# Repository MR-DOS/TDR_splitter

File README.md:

# TDR-splitter
----
## Description
Addon to te TDR_avalanche to allow simple measurement of cable reflections.

----
## Overview
This board should be used with the TDR-avalanche to measure cable reflections. The PCB includes trigger generator for the TDR_avalanche, passthrough USB for power supply and resistive splitter to allow connecting a cable and 50 Ohm terminated oscilloscope. The splitter offers 3 ports, 50 Ohm terminated. The signal passes directly over the CABLE port. Insertion loss of the splitter from IN to OUT port is about 20 dB.

----
## Features
### Resistive splitter
Already explained in overview.

### Trigger generator
The trigger generator can output 2, 4 or 8 kHz square wave. 8 kHz is recommended for the TDR_avalanche.

----
## How to use it with TDR_avalanche
Connect TDR_avalanche to the IN port and TRIG\_OUT port. Connect Mini USB B cable as power supply. Connect USB cable to the USB A port and connect the cable to TDR\_avalanche. Connect cable under test to CABLE port. Connect 50 Ohm terminated oscilloscope to the OUT port. Connect second oscilloscope input or trigger to SYNC\_OUT port of TDR\_avalanche. The TDR\_avalanche has to be modified to be usable with this board due to the high insertion loss - you have to remove both the attenuators so that in the emitter there are only the 2x 47R resistors and compensation network and there should be 27 Ohm resistor between output and the emitter network so that it is roughly 50 Ohm terminated (in fact, the termination heavily changes during the avalanche pulse, but this does not matter as long as reflections return after the pulse ends).

----
## How to use it with some other pulse generator
Connect pulser output to IN port, connect cable under test to the CABLE port. Connect oscilloscope to the OUT port. Separate trigger has to be provided by your pulser board.

----
## Images
Oscillogram of an unterminated (open) 50 Ohm cable:

Oscillogram of an unterminated (open) 50 Ohm cable with defect some 35 cm form the end caused by being heavily pressed using pliers:

Closeup of the assembled board with all cables connected (please note that the bad IC footprint is already corrected):

Both the TDR\_avalanche and TDR\_splitter connected:

----
## References
Sadly, nothing interesting here. I came up with the splitter in my head at 4AM in bed.

[Tweet with photos of the device in use](https://twitter.com/polasek_petr/status/1066757945915072512)

----
## Sidenotes
The PCB uses coplanar waveguide designed for use on standard 1.5 mm FR-4 substrate with 35 um copper (double-sided). It is not very carefully designed and does not give perfect match, but as a prototype, its performance was sufficient. You can modify it for whatever impedance you want, just follow this rule: connect parallel to each of the terminal ports resistor equal to 2x the load impedance, the series resistors should be 4/3x the load impedance and don't forget to update the coplanar waveguide according to the desired impedance.

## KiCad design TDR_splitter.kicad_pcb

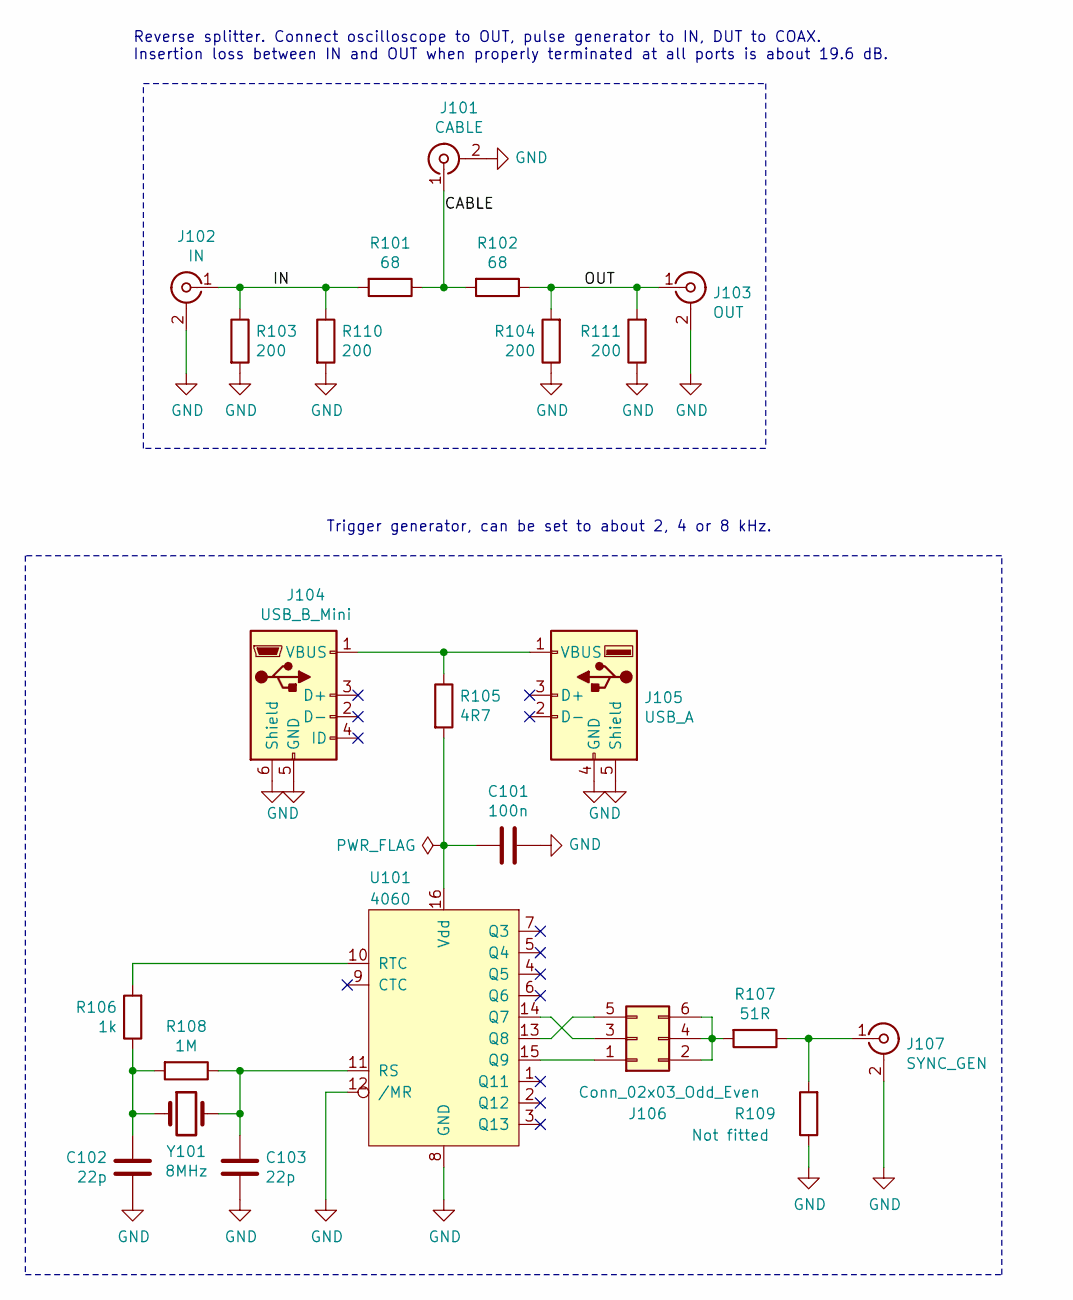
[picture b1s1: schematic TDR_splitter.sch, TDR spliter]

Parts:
C101: 100n; C_0805_2012Metric_Pad1.15x1.40mm_HandSolder
C102, C103: 22p; C_0805_2012Metric_Pad1.15x1.40mm_HandSolder
J101: CABLE; Molex_SMA_Jack_Edge_Mount_Chinese
J102: IN; Molex_SMA_Jack_Edge_Mount_Chinese
J103: OUT; Molex_SMA_Jack_Edge_Mount_Chinese
J104: USB_B_Mini; USB_Mini-B_Lumberg_2486_01_Horizontal
J105: USB_A; USB_A_CNCTech_1001-011-01101_Horizontal
J106: Conn_02x03_Odd_Even; PinHeader_2x03_P2.54mm_Vertical_SMD
J107: SYNC_GEN; Molex_SMA_Jack_Edge_Mount_Chinese
R101, R102: 68; R_0805_2012Metric_Pad1.15x1.40mm_HandSolder
R103, R104, R110, R111: 200; R_0805_2012Metric_Pad1.15x1.40mm_HandSolder
R105: 4R7; R_0805_2012Metric_Pad1.15x1.40mm_HandSolder
R106: 1k; R_0805_2012Metric_Pad1.15x1.40mm_HandSolder
R107: 51R; R_0805_2012Metric_Pad1.15x1.40mm_HandSolder
R108: 1M; R_0805_2012Metric_Pad1.15x1.40mm_HandSolder
R109: Not fitted; R_0805_2012Metric_Pad1.15x1.40mm_HandSolder
U101: 4060; SOIC-16_3.9x9.9mm_P1.27mm
Y101: 8MHz; Crystal_SMD_HC49-SD_HandSoldering

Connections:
/CABLE: J101.1 (In), R101.1, R102.2
/IN: J102.1 (In), R101.2, R103.1, R110.1
/OUT: J103.1 (In), R102.1, R104.2, R111.2
GND: C101.1, C102.2, C103.2, J101.2 (Ext), J102.2 (Ext), J103.2 (Ext), J104.5 (GND), J104.6 (Shield), J105.4 (GND), J105.5 (Shield), J107.2 (Ext), R103.2, R104.1, R109.1, R110.2, R111.1, U101.8 (GND), U101.12 (/MR)
unnamed: C101.2, R105.2, U101.16 (Vdd)
unnamed: C102.1, R106.1, R108.2, Y101.1
unnamed: C103.1, R108.1, U101.11 (RS), Y101.2
unnamed: J104.1 (VBUS), J105.1 (VBUS), R105.1
unnamed: J106.1, U101.15 (Q9)
unnamed: J106.2, J106.4, J106.6, R107.2
unnamed: J106.3, U101.14 (Q7)
unnamed: J106.5, U101.13 (Q8)
unnamed: J107.1 (In), R107.1, R109.2
unnamed: R106.2, U101.10 (RTC)

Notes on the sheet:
Trigger generator, can be set to about 2, 4 or 8 kHz.
Reverse splitter. Connect oscilloscope to OUT, pulse generator to IN, DUT to COAX. Insertion loss between IN and OUT when properly terminated at all ports is about 19.6 dB.

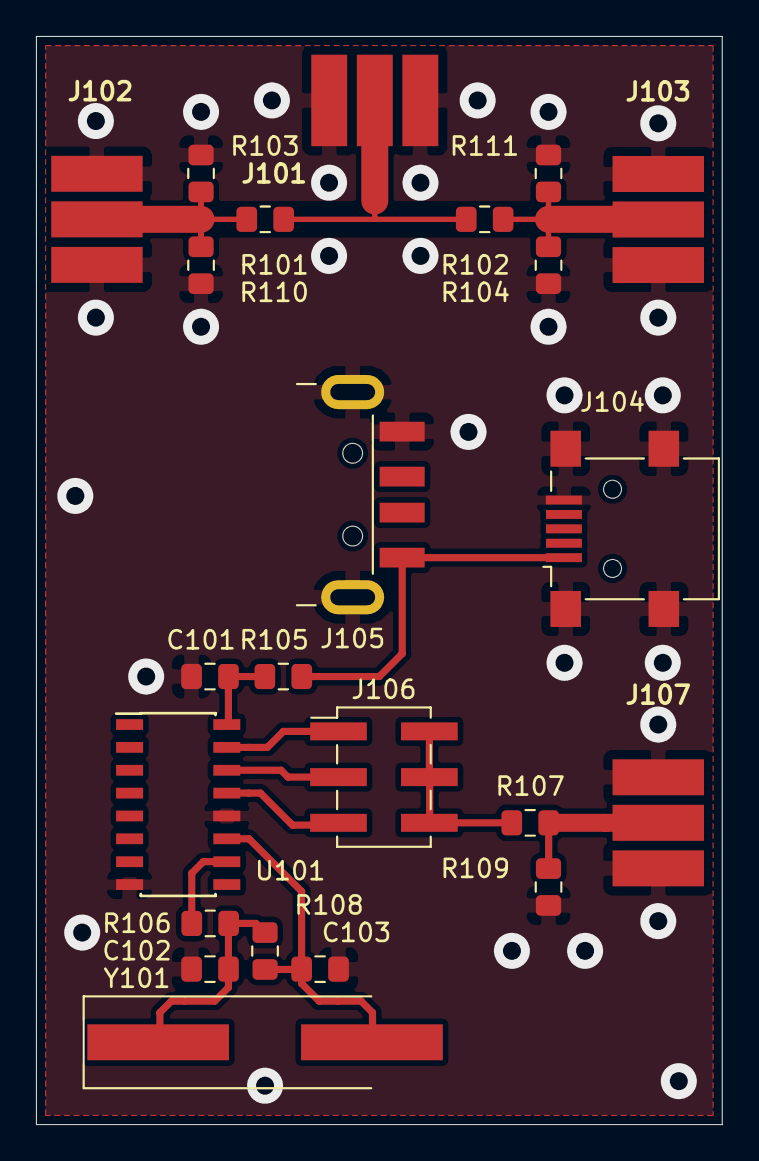
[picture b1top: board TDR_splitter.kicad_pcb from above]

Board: 2 copper layers, 38.1 x 60.5 mm, 23 parts (0 on the bottom side), 14 nets.

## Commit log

2018-12-05 Commit of the first tested version along with documentation.
2018-12-05 Fixed a typo in Sidenotes section
2019-02-13 Added schematic drawing in PDF
2021-11-23 Create LICENSE
    Added GPLv3 license
